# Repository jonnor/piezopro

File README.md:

Piezo module with integrated preamp in fully shielded package.

# Status
Developing first prototype

# TODO

Preamp Revision 2 testing

* Measure frequency response of amplifier with Bitscope
* Measure signal/noise ratio or noise floor.
* Test with 5V power supply
* Test overvoltage on connector. VGND,HOT,COLD

Preamp Revision 3

* Depending on test results
* Test a charge amplifier?
* Test a JFET directly on piezo?

Final revision

* Document test procedure for PCB and/or assembly.

## Questions

* PCB stackup retains piezo sensitivity.
Put piezo onto PCB. With glue? Use adhesive tape to attach to instrument.
Measure output level. Compare to without PCB. Compare to coppertape+covertape.
Maybe the bottom should just be piezo+coppertape, sides+top is PCB? Can still look "perfect" from outside.
* PCB stackup is a good way to shield.
Test having just a few (4) connected holes in mid layer (from top/bottom). Can noise get in? 50Hz
Emulate side-plated PCB using copper tape. How much does it improve?
* Frequency response should include resonant peak.
For 27mm element is as low as 4kHz, within fundamentals of piano. 12mm=9kHz. 9mm=18kHz, edge of human hearing.
How pronouced is this peak actually when mounted on instrument?

# Design test

Revision 1. gain. 220k/22k. 10M input.
20mm Murata. Piezo in tin, glued. Lying on top of guitar. 
Measured GND, HOT. on output.
low E string. 80mVpp sustained, 500mVpp attack
G string. 70mVpp sustained, 700mVpp attack
high E string. 70mVpp sustain, 800mVpp attack

Current consumption 0.68 mA.

## Learnings

* Basic circuit works. Both with balanced and unbalanced inputs.
* Using a tin box works well as a shield.
* With microphone level input, signal is too hot.

# Worklog

Rev1: Circuit design verification. 22 hours

* Sept 08. 4 hours. Research exiting designs, initial schematic.
* Sept 09. 4 hours. Part selection and initial layout.
* Sept 09. 1 / 4 hours. Setup simulation in KiCAD.
* Sept 14. 1 hour. Sketching piezo mounts with rim/center attach
* Sept 19. 7 hours. Assembly and testing revision 1 PCB.
* Sept 22. 2 hours. Test overvoltage, calculate new component values

Rev2: Assembly concept verification. 7 hours 

* Oct 4. 4 hours. Update schematic and layout for revision 2. 
* Oct 8. 3 hours. Go through revision 2.
* Oct 3. 1 / 4 hours. Find out how to import artwork in KiCAD

Rev3: Production tweaked

* March 16. 2 hours. Make Python tool for vias shielding, use instead of edge platings

# Requirements

Electronics

* PCB is an enclosure for 20mm piezo. 25mm outer diameter
* BOM max 3 USD
* 100 hours++ on 9V battery. Max 2mA avg draw
* Low noise
* Balanced output. But also works with unbalanced inputs
* Line-level output, +4dBU
* 20Hz-20kHz bandwidth
* Reverse polarity protection
* Input overvoltage protection

Mechanics

* Cylindrical
* Fully shielded
* Output: 1/4" TRS female
* Power: 9V battery clip
* 1m cable, soft/flexible

# Sourcing

* Capacitors.
[0.1uF](https://no.farnell.com/w/c/passive-components/capacitors/ceramic-capacitors/smd-ceramic-multilayer-mlcc-capacitors?capacitance=0.1uf&voltage-rating=25v|35v&range=inc-in-stock-grp1&sort=P_PRICE)
[10uF](https://no.farnell.com/w/c/passive-components/capacitors/ceramic-capacitors/smd-ceramic-multilayer-mlcc-capacitors?capacitance=10uf&voltage-rating=6.3v|10v|25v|35v&range=inc-in-stock-grp1&sort=P_PRICE)
* NMOS. [BSS138L](https://no.farnell.com/on-semiconductor/bss138lt1g/mosfet-n-50v-0-2a-sot-23/dp/1431319)
* Diodes [SOD-532](https://no.farnell.com/w/c/semiconductors-discretes/diodes/small-signal-diodes?diode-case-style=sod-523|sod-523f&no-of-pins=2pins|3pins&packaging=cuttape&range=inc-in-stock-grp1|exc-obs&sort=P_PRICE)
*  Zeners [SOD-523](https://no.farnell.com/w/c/semiconductors-discretes/diodes/zener-single-diodes?zener-voltage-vz-typ=3.3v|3.6v|3.9v|4.3v|4.7v|5.1v&diode-case-style=sod-523|sod-523f&no-of-pins=2pins|3pins&packaging=cuttape&range=inc-in-stock&sort=P_PRICE)
* Opamp. [TL062](https://no.farnell.com/search/prl/results?packaging=cuttape&range=inc-in-stock&st=tl062&sort=P_PRICE)
* Piezo [Farnell](https://no.farnell.com/w/c/sensors-transducers/transducers/sensing-transducers/piezo-transducer-elements?external-diameter=27mm|35mm&range=inc-in-stock)

# BOM

[Octopart BOM](https://octopart.com/bom-tool/TbIQ2Cbo/OKDwL97yteywY4BA)

## Testing

Testing aspects

* PCB design verification
* Enclosure/mount design verification
* Production checks.

Tough-but-normal conditions

* 3-8 microphones
* Plugged into standard mixer with 50m cable
* 1 9V battery per microphone

Reverse polarity:
Hold battery on wrong way for 10 seconds, plug right way, ensure works OK.

Overvoltage:
Hit piezo with hammer. Ensure performance good afterwards.

Frequency response:
Connect signal generator at PCB input, with capacitor simulating piezo capacitance.
Sweep sinewave, record output, calculate frequency response.

Noise.
Internal noise. No signal. Measure output
Injected noise/interference (on output line, at microphone).
Attempt to inject 50Hz by wire. Lightbubl+dimmer.
Measure without shielding, and with.

## References

Electronics

* [Elliot Sound Products: Balanced Line Driver](http://sound.whsites.net/articles/dwopa3.htm#s10)
* [Elliot Sound Products: High-Z ](http://sound.whsites.net/articles/high-z.html)
* [WikiPedia: Line level](https://en.wikipedia.org/wiki/Line_level). Consumer: -10dBV 0.894 Vpp, Pro: +4dBu 3.472
* [StackExchange.com: Piezo FET preamp balanced output](https://sound.stackexchange.com/questions/687/diy-contact-microphone/37714#37714).
Developed by Alex Rice, www.zachpoff.com/diy-resources/alex-rice-piezo-preamplifier/.
Extremely simple design. Used as base for DIY kits and complete microphone Cortado MkII from Zeppelin Labs. 
* [Elliot Sound Products: Piezo Pickup Preamplifiers](https://sound-au.com/project202.htm).
Tested high-Z preamp versus Charge Amplifier.
First opamp stage is charge amp with 1x gain, then second stage sets desired gain.
Found that high-Z would pick up (50hz) hum, where as charge amplifier did not. When piezo was connected with bare leads.
Tested with TL072 and found it very quiet.

Shielding

* [Shielding fabric](https://www.aliexpress.com/item/Emf-shielding-Fabric-Signal-Block-Fabric-Military-Nickel-Fabric/32795159060.html)
* [Shielding paint](https://www.stewmac.com/Pickups_and_Electronics/Shielding/Conductive_Shielding_Paint.html)

Simulation

* [ngspice: Using KiCAD as GUI](http://ngspice.sourceforge.net/ngspice-eeschema.html)
* [eCircuitCenter: Basic SPICE opamp model](http://www.ecircuitcenter.com/Circuits/opmodel1/opmodel2.htm)
* [WikiPedia: Piezoelectric sensor](https://en.wikipedia.org/wiki/Piezoelectric_sensor).
Basic model (disregards resonance): Voltage source with a capacitor in series.

## Existing products

Active contact microphones

- Schertler. [Thommann](https://www.thomann.de/gb/schertler_dyn_uni_p48_contact_microphone.htm).
48V phantom power.
310 EUR.
- Cortado MkII [from Zeppelin Labs](https://zeppelindesignlabs.com/product/cortado-mkiii-contact-microphone/).
48V phantom power. Two gain settings, low-frequency cutoff switch.
150 USD assembled.
- K&K Pure pickup plus K&K Pure preamp. [Thommann](https://www.thomannmusic.no/kk_pure_preamp.htm?sid=fd268c89787f256dcc79b210d18a3667).
Total around 300 EUR

# Usage ideas

* Guitar. Acoustic, electric, traveller.
* DIY Cigarbox
* CNC mill an electric travel guitar from single piece of wood. Rosewood/maple.
https://www.aliexpress.com/item/Hot-Sale-Custom-Electric-Travel-Guitar-Portable-Style-Rosewood-Fretboard-22-Frets-with-Soft-Bag-can/32803999609.html
* Violin,viola,chello. 
* Double bass. 
* Stomp box

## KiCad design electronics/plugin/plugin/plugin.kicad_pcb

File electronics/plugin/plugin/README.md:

# Plug-in-power

Contains a single JFET buffer, designed to be powered from "Plug in power" (PIP) at 3-5 volts.
Very similar to off-the-shelf electret microphone modules are done.
Can be directly plugged into a device with mic-level input supporting PIP.
Such as a portable recorder, PC, phone or laptop.
Or use preamps or adapters designed for electret microphones.

Board designed to be soldered directly to piezo element, using castellated edge holes.
The assembly should then protected mechanically using silicone etc,
and be shielded completely using copper tape.
And potentially coated with plastidip et.c. to be fully waterproof.
Output is a NN cm long cable with 3.5 mm TRRS male.

## TODO

- Adapt circuit to have trimpot for Rs
- Select and order components. Follow Zack Hoff PIP amp. JFET: 2SK209
- Make and test initial circuit
- Measure gain, noise levels

## Open questions

- Does this two-step amplified design work give good quality? First JFET buffer, then external preamp?
Test the circuit externally.
Test how copper shielding affects.
Over just the piezo. Over piezo, and PCB separate. Over piezo and PCB integrated.

- How is sound pickup influenced by mounting PCB onto the piezo?

Alternative fully-integrated design.
Put everything needed also for P48V phantom power and 9V.
Then just have different sets of wires coming out for different connectivity options.

## Challenges

Multiple usage scenarios with different expectations of connection

- Instrument. 9V battery + female jack
- XLR with phantom power
- Portable recorder. Plug-in-power. Though some also have XLR or TRS

Different usage scenarious may have different input level,
and require different gain

- Ambient listening. High sensitivity desired
- Stringed/plucked instruments. Guitar, kaliba, piano etc. Relatively loud
- Percussive instruments. Very loud / high energy

## Learnings

### Direct soldering

06.08.2023. Tested soldering a PCB board with castellated holes directly to a PCB.
Worked quite nicely. Heated the PCB castellated first, then feed solder on pad, then towards piezo.
Used 280 deg C soldering iron, was sufficient.

## Components

#### SMD JFET for audio

SOT23 DSG: Gate on tip

- 2SK3557 - SOT23 DSG
- MMBF4416A - SOT23 DSG
- MMBF5484/MMBF5485/MMBF5486 - SOT23 DSG. 5484 has lowest VGS_off - good
- MMBFJ309/MMBFJ310 - SOT23 DSG. 309 has lowest VGS_off - good
- MMBF4393LT1G - SOT23 DSG
- MMBFJ201 - SOT23 DSG.
- SST201 - SOT23. Low cutoff voltage
- LSBF510 - SOT23. Low cutoff voltage
- 2N4117

Very expensive

- sst310

Discontinued

- MMBF4393
- Philips bf512
- MMBF4416
- BF256B
- BF862
- BF556

Specialiy

- JFE150 SOT23-5. Modern. Includes clamping diodes

Electret Capsule Microphone (ECM) specialized

- 2SK208. SOT23. Pin order different? No proction diodes. Normally in stock Digikey.
- 2SK1109. SOT23. Comes with binning of IDDS. Obsolete? 
- TF256TH. One diode internally. Comes with binning of IDDS. SC-106A SMD. Obsolete?
- NTE2917. TO92S

Others by others with success

- 2SK209. By Zack Hoff

## References

### Zack Poff: PIP Stereo Piezo Preamplifier

https://www.zachpoff.com/resources/pip-stereo-piezo-preamplifier/

Very simple circuit.
JFET, Zeners for protection.
Mentions possibility of adding a capacitor on Rs to increase gain.
Used the 2SK209 SMD JFET (IDSS grade Y). After testing many others.
Zeners are back-to-back. 5.1V
Stereo. Two channels on single PCB.
Have to solder inputs and outputs to wires. No connectors.
3d-printed enclosure.
Has a "pad" switch. Pulls some capacitors to ground.
Says there is sufficient gain for quiet sources. But not the best for percussive. Presumably overloading output.

!! He has tested the spread of the JFETs.
They should be measured and binned by IDSS, for best results.

Excellent starting point for an inline PIP preamp.
Would instead use 3.5 mm female jacks. SMT, avoid soldering cable.
Also tweaking the enclosure and PCB to make shielding trivial. 
Copper foil/tape that connects to PCB. Solder one spot and then press-connect.
And order it pre-made at JLCPCB etc.

His preamp was used in combination with below DYI piezos.

### 3D-Printed DIY Contact Microphone

https://www.zachpoff.com/resources/3d-printed-diy-contact-microphone/
27mm piezo disk.
Glued to 1-1/8″ dia Aluminum discs. Approx 29 mm.
3D-printed back shells.
The alu disc makes them quite sturdy. Also also reduces the reasonant peak. At the expense of some sensitivity.
?? No shielding in the enclosure. Not mentioned the effect of this.
Tested by students over many years.

Seems like a very practical construction.

### Elliot Sound: JFET amplifier design
https://sound-au.com/articles/jfet-design.htm#s3

Most important JFET parameters:

- the gate-source cutoff voltage VGS (off). Aka  'pinch-off' voltage (VP).
- and the maximum current with zero gate voltage (IDSS).

Must in practice be measured.
Large amount of unit variation in these. 
Shows a practical test circuits to measure the key parameters.

Lots of discussion on how to set bias point (via selecting R_s).
Recommends a trim-pot for R_s.

The lower the supply voltage, the more accurate the biasing needs to be.

## Bias point and component selection

In this applicaion there will also be some external variation in R_s on,
so the circuit must be robust to a reasonable range of these.
Complicates testing of the bias point. 

In practice JFET selection is likely to be critical.
And it is quite likely that JFETs must be measured/binned.

=> this design is only ideal when direct operation as "elecret" mic is needed.
If an external power source is acceptable, then a op-amp based charge amplifier is better.

Gain adjustment has to be primarily done by selecting another JFET.
The other option is to use the resistive divider on the input,
but this reduces SNR. 

## Accessories

#### XLR converter

PIP 3.5mm TRS to XLR phantom power

- Rode VXLR+
https://www.thomann.de/be/rode_vxlr_416774.htm
- Movo FXLR-PRO 
- Boya 35C-XLR

#### Battery box

Ideally with jack socket (female).
For guitar amp etc connection.

Not so much completely ready??

- MC-401 condenser mic mixer. 4 in, 1 out
- MC33202 Dynamic Condenser Microphone Preamplifier. 1 elecret input 
- Soundman A3 adapter?
- Soundprofessionsals SP-SPSB-1
https://soundprofessionals.com/product-category/microphone-power-modules-battery-modules/

There are a bunch of ready-made electret amplifier boards

- 3V/5V/12V Input MAX9812 Electret Microphone Amplifier
- LM358

Would need to add minijack input, jack output, and 9V battery connector.

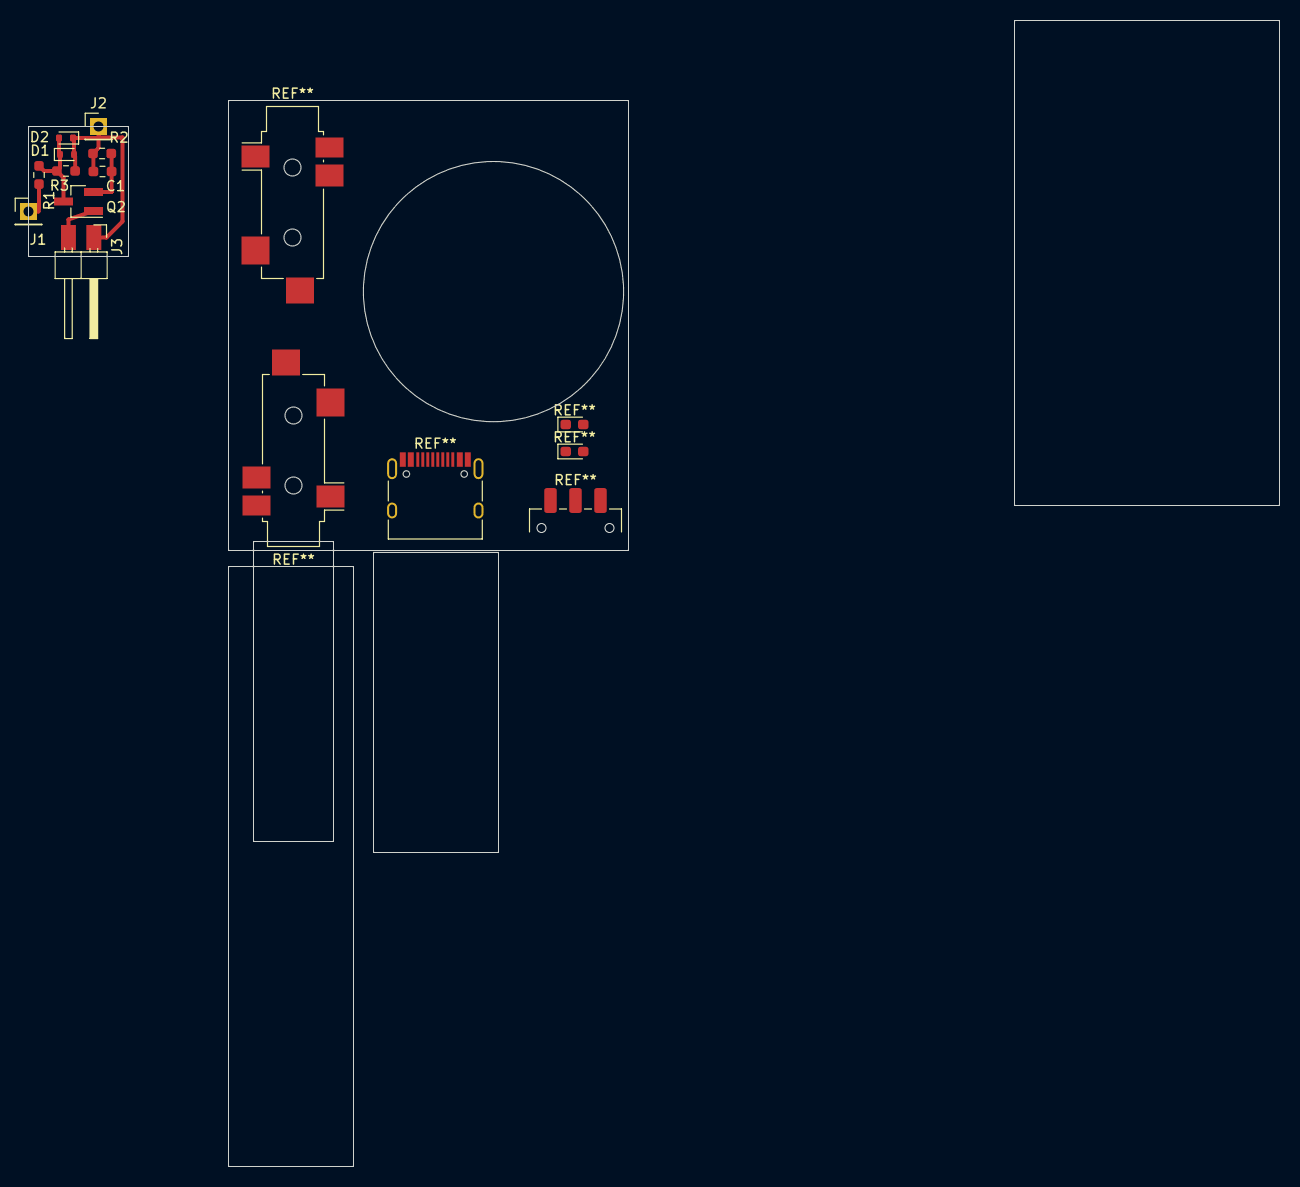
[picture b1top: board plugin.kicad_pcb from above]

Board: 2 copper layers, 125.1 x 114.6 mm, 10 parts (0 on the bottom side), 5 nets.

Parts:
C1: C; R_0603_1608Metric_Pad0.98x0.95mm_HandSolder
D1, D2: D; D_SOD-523
J1, J2: Conn_01x01; PinHeader_1x01_P2.54mm_Vertical
J3: Conn_01x02; PinHeader_1x02_P2.54mm_Horizontal
Q2: Q_NMOS_DSG; SOT-23_Handsoldering
R1: 100; R_0603_1608Metric_Pad0.98x0.95mm_HandSolder
R2: R; R_0603_1608Metric_Pad0.98x0.95mm_HandSolder
R3: 1M; R_0603_1608Metric_Pad0.98x0.95mm_HandSolder

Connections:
/GATE: D1.1 (K), D2.2 (A), Q2.3 (G), R1.2, R3.1
/OUT: J3.2, Q2.1 (D)
GND: C1.2, D1.2 (A), D2.1 (K), J2.1, J3.1, R2.2, R3.2
unnamed: J1.1, R1.1
unnamed: C1.1, Q2.2 (S), R2.1

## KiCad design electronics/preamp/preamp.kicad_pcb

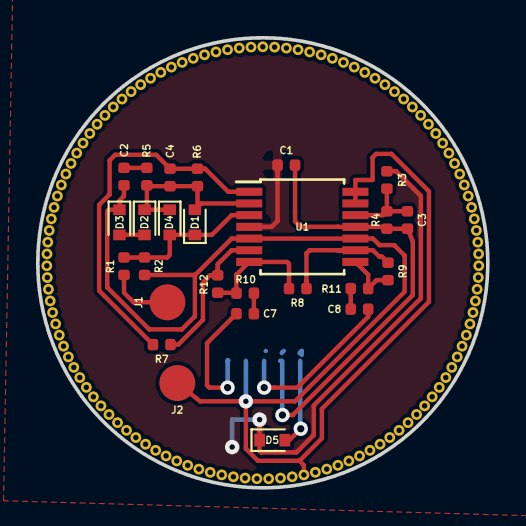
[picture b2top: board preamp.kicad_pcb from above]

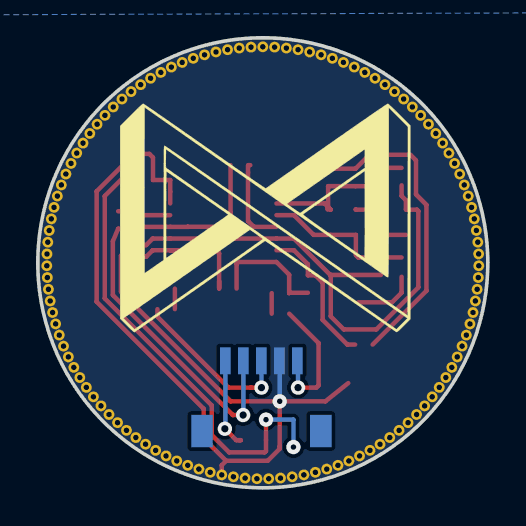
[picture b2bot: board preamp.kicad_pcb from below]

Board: 2 copper layers, 25.0 x 25.0 mm, 28 parts (2 on the bottom side), 19 nets.

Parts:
C1, C3: 0.1uF 15V; C_0402_1005Metric
C2: 1uF; C_0402_1005Metric
C4: 1000pF; C_0402_1005Metric
C7, C8: 10uF; C_0402_1005Metric
D1, D4, D5: D; D_SOD-523
D2, D3: Zener 3V1; D_SOD-523
J1, J2: Conn_01x01; TestPoint_THTPad_1.0x1.0mm_Drill0.5mm
J3: Conn_01x05; Molex_Pico-Clasp_202396-0507_1x05-1MP_P1.00mm_Horizontal_No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
J4: Conn_01x01; viashield
R1, R3, R4, R5, R6, R7: 12k; R_0402_1005Metric
R2: 10M; R_0402_1005Metric
R8, R9: 100k 1%; R_0402_1005Metric
R10, R11: 100 1%; R_0402_1005Metric
R12: 27k; R_0402_1005Metric
U1: TL064; TSSOP-14_4.4x5mm_P0.65mm

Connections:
+BATT: D5.2, J3.1
-BATT: C1.2, C3.2, J3.2, R4.2, U1.11
/AMP: C4.2, R6.1, R7.2, U1.1
/BUF+: R8.2, R10.2, R12.1, U1.7
/BUF-: R9.1, R11.2, U1.8
/GAIN-: R7.1, R12.2, U1.6
/IN+: J1.1, R1.2
/INV-: R8.1, R9.2, U1.9
/OUT+: C7.1, J3.5
/OUT-: C8.1, J3.3
/PRE+: D1.1, D4.2, R1.1, R2.2, U1.3
/PRE-: C4.1, D1.2, D2.1, D4.1, R5.2, R6.2, U1.2
/VGNDREF: C3.1, R3.2, R4.1, U1.12
unnamed: C2.1, R5.1
unnamed: C7.2, R10.1
unnamed: C8.2, R11.1
unnamed: D2.2, D3.2
VCC: C1.1, D5.1, R3.1, U1.4
VGND: C2.2, D3.1, J2.1, J3.4, J4.1, R2.1, U1.5, U1.10, U1.13, U1.14

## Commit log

2018-09-08 Initial schematic
2018-09-09 Add reverse polarity protect
2018-09-09 Output caps, fix opamp annotations
2018-09-09 Initial layout concept
2018-09-09 Tweak component placement
2018-09-09 Simulation was performed, tweak some values
2018-09-09 Initial routing
2018-09-09 Tweak routing a little bit
2018-09-09 Ready to make first proto
2018-09-15 Add production files for revision 1
2018-09-15 Change to 100 ohm on input
2018-09-20 Rev1 testing started
2018-09-20 More useful label positions for placing components
2018-09-22 Input overvoltage tested
2018-09-22 Model narrower frequency response with lower gain
2018-10-04 preamp: Rev2 started
2018-10-04 preamp: Updated layout
2018-10-04 preamp: Tweaks for BOM
2018-10-04 preamp: Tweak
2018-10-04 phantomxlr: Basic circuit idea
2018-10-08 preamp: Tweak layout
2018-10-08 README: Update
2018-10-08 preamp: Cleanup layout a bit
2018-10-18 preamp: Add artwork
    - Import PNG into bitmap2component
    - Adjust tresholds to export mask and silkscreen
    - Merge the two files into one kicad_mod
    - Import the footprint, flip to back and rotate
2018-10-18 preamp: Add edge plating connector
2018-10-18 README: Update worklog
2018-11-27 preamp: Import highres artwork
2018-11-27 preamp: Add 3d-model of connector
2018-11-27 Fix artwork being wrong size
2019-01-28 preamp: Move via under connector
2019-01-28 preamp: Update copper fills
2019-03-16 preamp: Add script for generating shield using vias
2019-03-16 Compress and prettify traces
2019-03-16 preamp: Use via shield
2019-03-16 preamp: Move last via underneath connector
2019-03-16 Update workhours
2021-06-02 README: Update with some existing products and designs
2021-06-22 doc: Add some notes
2023-06-24 Add some notes
2023-06-24 plugin: Add new preamp concept
2023-08-06 plugin: Fix protection, notes on solder test and JFET amp setup
2024-05-30 Add some notes on PIP and a separate battery-powered preamp
